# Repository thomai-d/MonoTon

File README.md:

# MonoTon
Arduino based step sequencer and software-synth

Video on youtube:

[(Audio only)](https://github.com/thomai-d/MonoTon/blob/master/media/MonoTon1.mp3).

## Features
* 8 instruments (Kick, Hat, Snare, Shaker, Clap, Noise, Sine, Square)
* Each instrument has 4 banks a 16 steps each and can be muted
* Synthesis using 8bit wavetables
* 20000Hz sampling rate
* Master is filtered through analog high-pass filter (2pole)

## Hardware
* atmega1284 @ 16MHz using [Mighty1284 platform](https://github.com/maniacbug/mighty-1284p)
* lots of 74HC595 shift registers (for LEDs)
* MCP23S17 port extenders (for buttons)
* CD4067 multiplexer (for analog potis)
* R2R network for D/A conversion
* Some eagle files included

## Lessons learned while developing
* The analog inputs are quite noisy. De-noising uses quite much cpu.
* Don't ever solder this much wires by hand. PCB services are your friend.
* Prefer [DDS](http://interface.khm.de/index.php/lab/interfaces-advanced/arduino-dds-sinewave-generator/) over an R2R ladder.

## Open bugs / flaws
* Although the output is buffered by an opamp, the sound sounds distorted when using the PC's line in. If I conntect it directly to the speakers, the sound is quite clear.

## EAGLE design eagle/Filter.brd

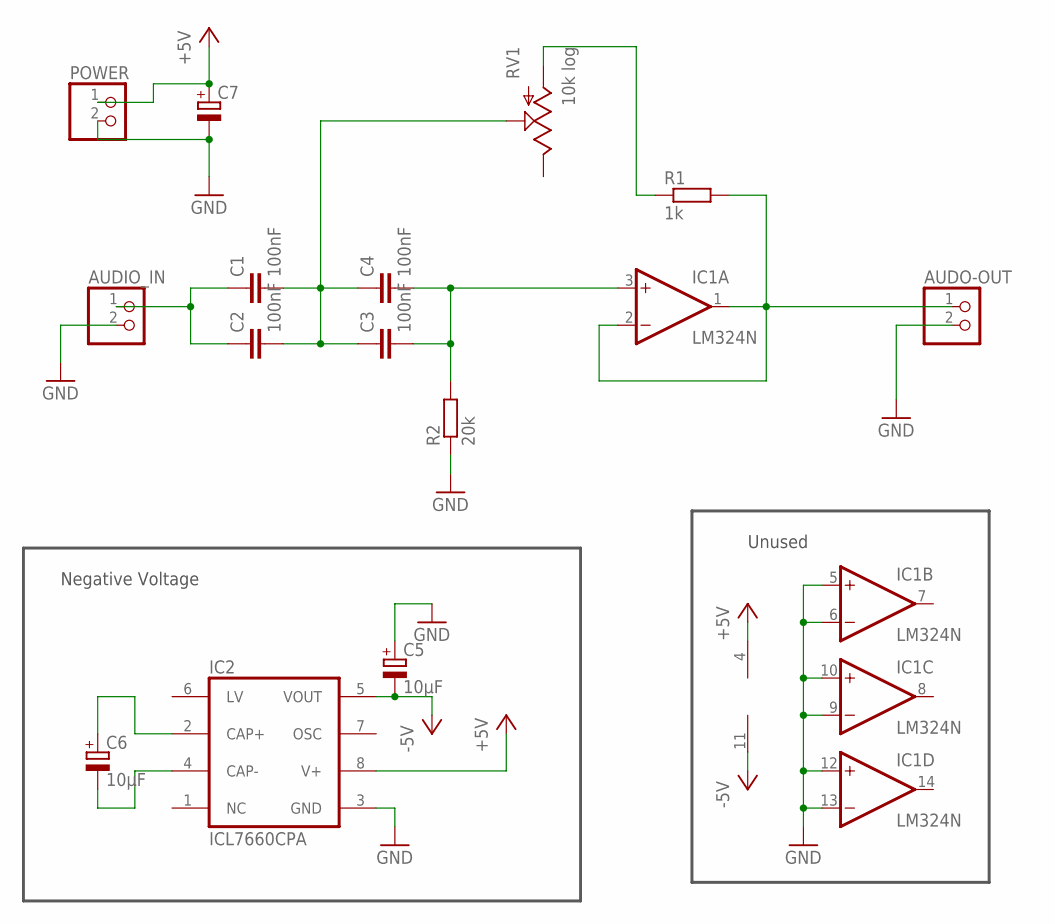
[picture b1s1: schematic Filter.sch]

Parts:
AUDIO_IN: PINHD-1X2; 1X02
AUDO-OUT: PINHD-1X2; 1X02
C1, C2, C3, C4: 100nF; C025-025X050
C5, C6: 10µF; E2,5-6
C7: CPOL-EUE2.5-6; E2,5-6
IC1: LM324N; DIL14
IC2: ICL7660CPA; DIL08
POWER: PINHD-1X2; 1X02
R1: 1k; 0207/7
R2: 20k; 0207/7
RV1: 10k log; ALPS_POT

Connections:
+5V: C7.+, IC1.4 (V+), IC2.8 (V+), POWER.1
-5V: C5.-, IC1.11 (V-), IC2.5 (VOUT)
GND: AUDIO_IN.2, AUDO-OUT.2, C5.+, C7.-, IC1.5 (+IN), IC1.6 (-IN), IC1.9 (-IN), IC1.10 (+IN), IC1.12 (+IN), IC1.13 (-IN), IC2.3 (GND), POWER.2, R2.1
unnamed: C3.2, C4.2, IC1.3 (+IN), R2.2
unnamed: AUDIO_IN.1, C1.1, C2.1
unnamed: C1.2, C2.2, C3.1, C4.1, RV1.P$2 (S)
unnamed: AUDO-OUT.1, IC1.1 (OUT), IC1.2 (-IN), R1.2
unnamed: R1.1, RV1.P$3 (A)
unnamed: C6.+, IC2.2 (CAP+)
unnamed: C6.-, IC2.4 (CAP-)

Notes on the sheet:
Unused
Negative Voltage

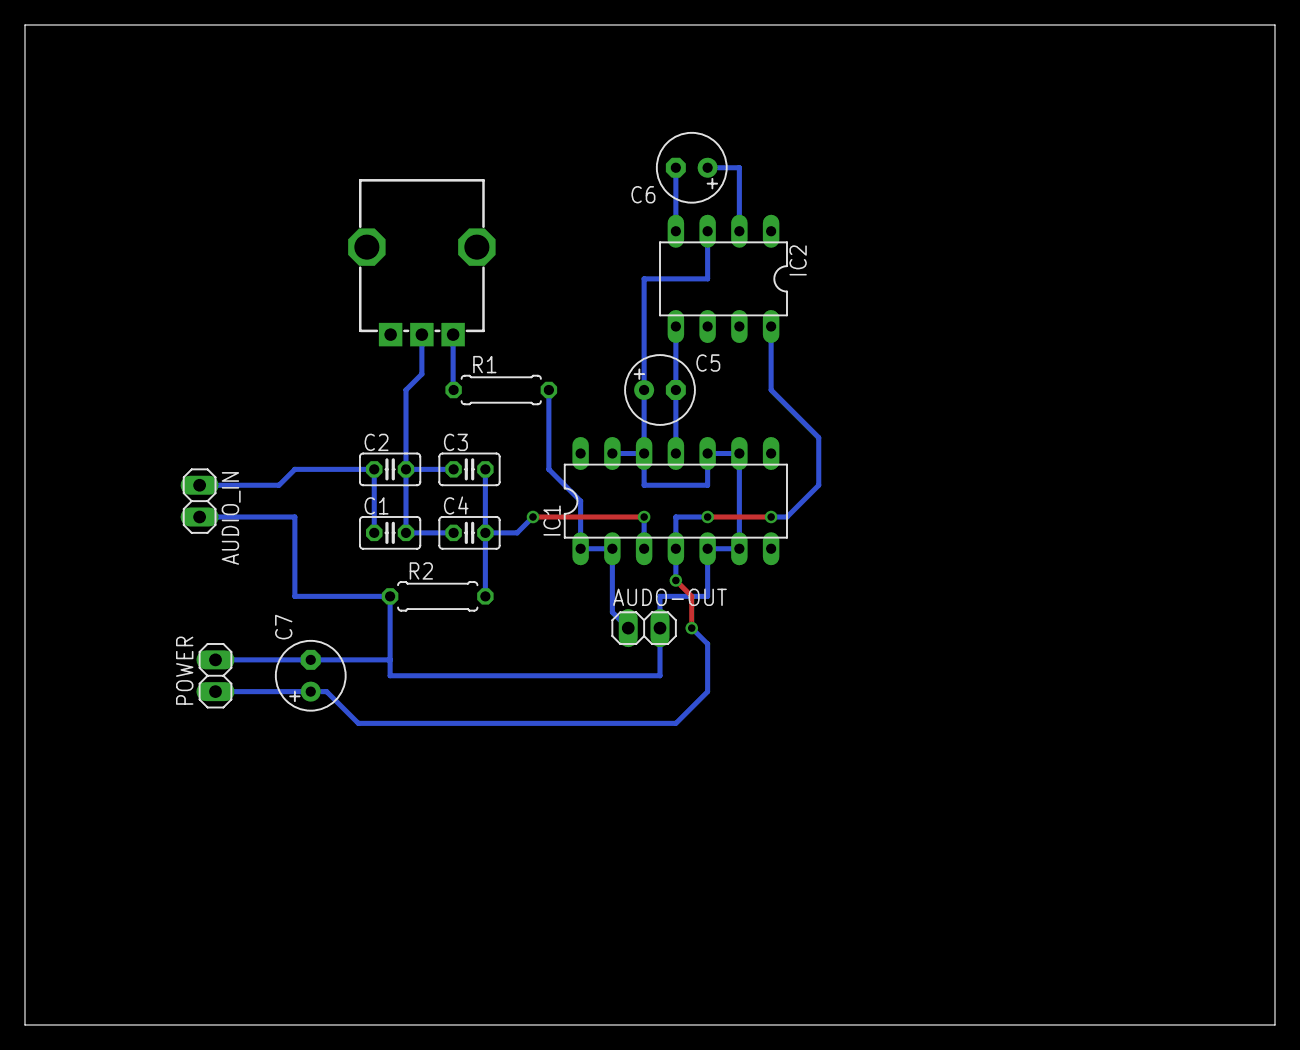
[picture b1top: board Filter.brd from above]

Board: 2 copper layers, 100.0 x 80.0 mm, 15 parts (0 on the bottom side), 10 nets.

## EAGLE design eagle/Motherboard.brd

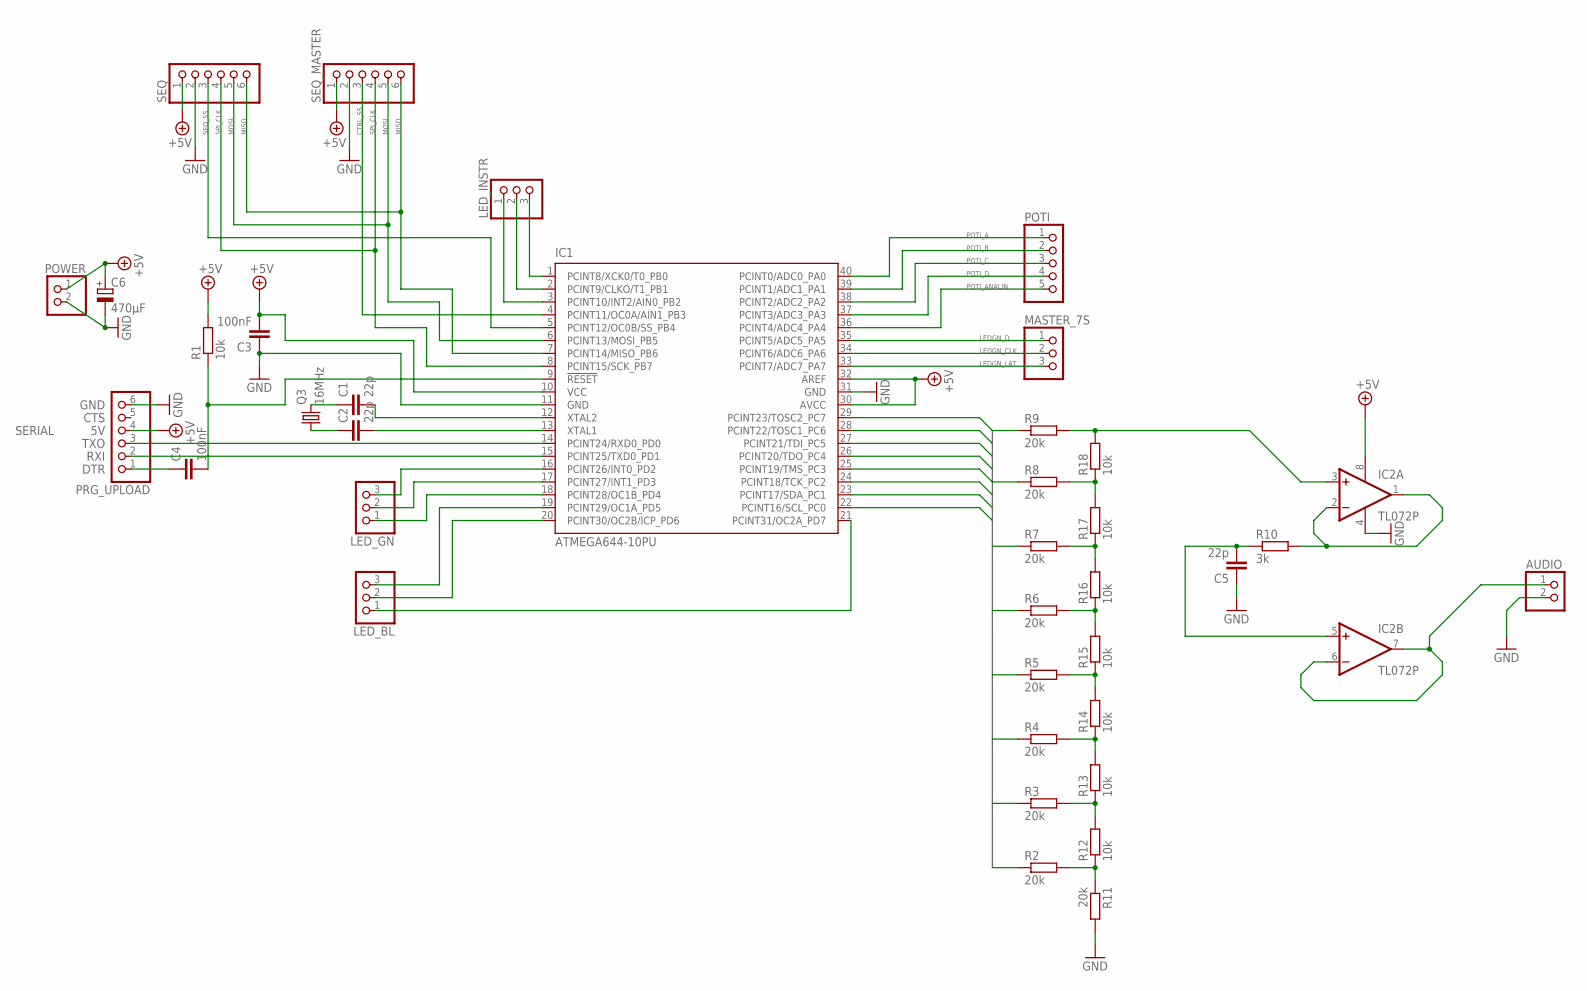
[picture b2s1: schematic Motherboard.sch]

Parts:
AUDIO: PINHD-1X2; 1X02
C1, C2, C5: 22p; C025-060X050
C3, C4: 100nF; C025-060X050
C6: 470µF; E3,5-10
IC1: ATMEGA644-10PU; DIL40
IC2: TL072P; DIL08
LED_BL: PINHD-1X3; 1X03
LED_GN: PINHD-1X3; 1X03
LED_INSTR: PINHD-1X3; 1X03
MASTER_7S: PINHD-1X3; 1X03
POTI: PINHD-1X5; 1X05
POWER: PINHD-1X2; 1X02
PRG_UPLOAD: PINHD-1X6; 1X06
Q3: 16MHz; HC18U-V
R1, R12, R13, R14, R15, R16, R17, R18: 10k; 0204/7
R2, R3, R4, R5, R6, R7, R8, R9, R11: 20k; 0204/7
R10: 3k; 0204/7
SEQ: PINHD-1X6; 1X06
SEQ_MASTER: PINHD-1X6; 1X06

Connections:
+5V: C3.2, C6.+, IC1.10 (VCC), IC1.30 (AVCC), IC1.32 (AREF), IC2.8 (V+), POWER.1, PRG_UPLOAD.4, R1.2, SEQ.1, SEQ_MASTER.1
CTRL_SS: IC1.4 (PCINT11/OC0A/AIN1_PB3), SEQ_MASTER.3
DA0: IC1.22 (PCINT16/SCL_PC0), R2.1
DA1: IC1.23 (PCINT17/SDA_PC1), R3.1
DA2: IC1.24 (PCINT18/TCK_PC2), R4.1
DA3: IC1.25 (PCINT19/TMS_PC3), R5.1
DA4: IC1.26 (PCINT20/TDO_PC4), R6.1
DA5: IC1.27 (PCINT21/TDI_PC5), R7.1
DA6: IC1.28 (PCINT22/TOSC1_PC6), R8.1
DA7: IC1.29 (PCINT23/TOSC2_PC7), R9.1
GND: AUDIO.2, C3.1, C5.1, C6.-, IC1.11 (GND), IC1.31 (GND), IC2.4 (V-), POWER.2, PRG_UPLOAD.6, R11.2, SEQ.2, SEQ_MASTER.2
LEDGN_CLK: IC1.34 (PCINT6/ADC6_PA6), MASTER_7S.2
LEDGN_D: IC1.35 (PCINT5/ADC5_PA5), MASTER_7S.1
LEDGN_LAT: IC1.33 (PCINT7/ADC7_PA7), MASTER_7S.3
MISO: IC1.7 (PCINT14/MISO_PB6), SEQ.6, SEQ_MASTER.6
MOSI: IC1.6 (PCINT13/MOSI_PB5), SEQ.5, SEQ_MASTER.5
unnamed: C1.1, Q3.2
unnamed: C2.1, Q3.1
unnamed: C2.2, IC1.13 (XTAL1)
unnamed: C1.2, IC1.12 (XTAL2)
unnamed: R3.2, R12.2, R13.1
unnamed: R4.2, R13.2, R14.1
unnamed: R5.2, R14.2, R15.1
unnamed: R6.2, R15.2, R16.1
unnamed: IC1.1 (PCINT8/XCK0/T0_PB0), LED_INSTR.3
unnamed: IC1.2 (PCINT9/CLKO/T1_PB1), LED_INSTR.2
unnamed: IC1.3 (PCINT10/INT2/AIN0_PB2), LED_INSTR.1
unnamed: R7.2, R16.2, R17.1
unnamed: R8.2, R17.2, R18.1
unnamed: R2.2, R11.1, R12.1
unnamed: IC2.3 (+IN), R9.2, R18.2
unnamed: IC2.1 (OUT), IC2.2 (-IN), R10.2
unnamed: IC1.16 (PCINT26/INT0_PD2), LED_GN.3
unnamed: IC1.17 (PCINT27/INT1_PD3), LED_GN.2
unnamed: IC1.18 (PCINT28/OC1B_PD4), LED_GN.1
unnamed: IC1.19 (PCINT29/OC1A_PD5), LED_BL.3
unnamed: IC1.20 (PCINT30/OC2B/ICP_PD6), LED_BL.2
unnamed: IC1.21 (PCINT31/OC2A_PD7), LED_BL.1
unnamed: C5.2, IC2.5 (+IN), R10.1
unnamed: AUDIO.1, IC2.6 (-IN), IC2.7 (OUT)
POTI_A: IC1.40 (PCINT0/ADC0_PA0), POTI.1
POTI_ANALIN: IC1.36 (PCINT4/ADC4_PA4), POTI.5
POTI_B: IC1.39 (PCINT1/ADC1_PA1), POTI.2
POTI_C: IC1.38 (PCINT2/ADC2_PA2), POTI.3
POTI_D: IC1.37 (PCINT3/ADC3_PA3), POTI.4
RESET: C4.2, IC1.9 (!RESET), R1.1
SEQ_SS: IC1.5 (PCINT12/OC0B/SS_PB4), SEQ.3
SPI_CLK: IC1.8 (PCINT15/SCK_PB7), SEQ.4, SEQ_MASTER.4
UPLOAD_DTR: C4.1, PRG_UPLOAD.1
UPLOAD_RXI: IC1.15 (PCINT25/TXD0_PD1), PRG_UPLOAD.2
UPLOAD_TXO: IC1.14 (PCINT24/RXD0_PD0), PRG_UPLOAD.3

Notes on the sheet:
GND
CTS
TXO
RXI
DTR
SERIAL

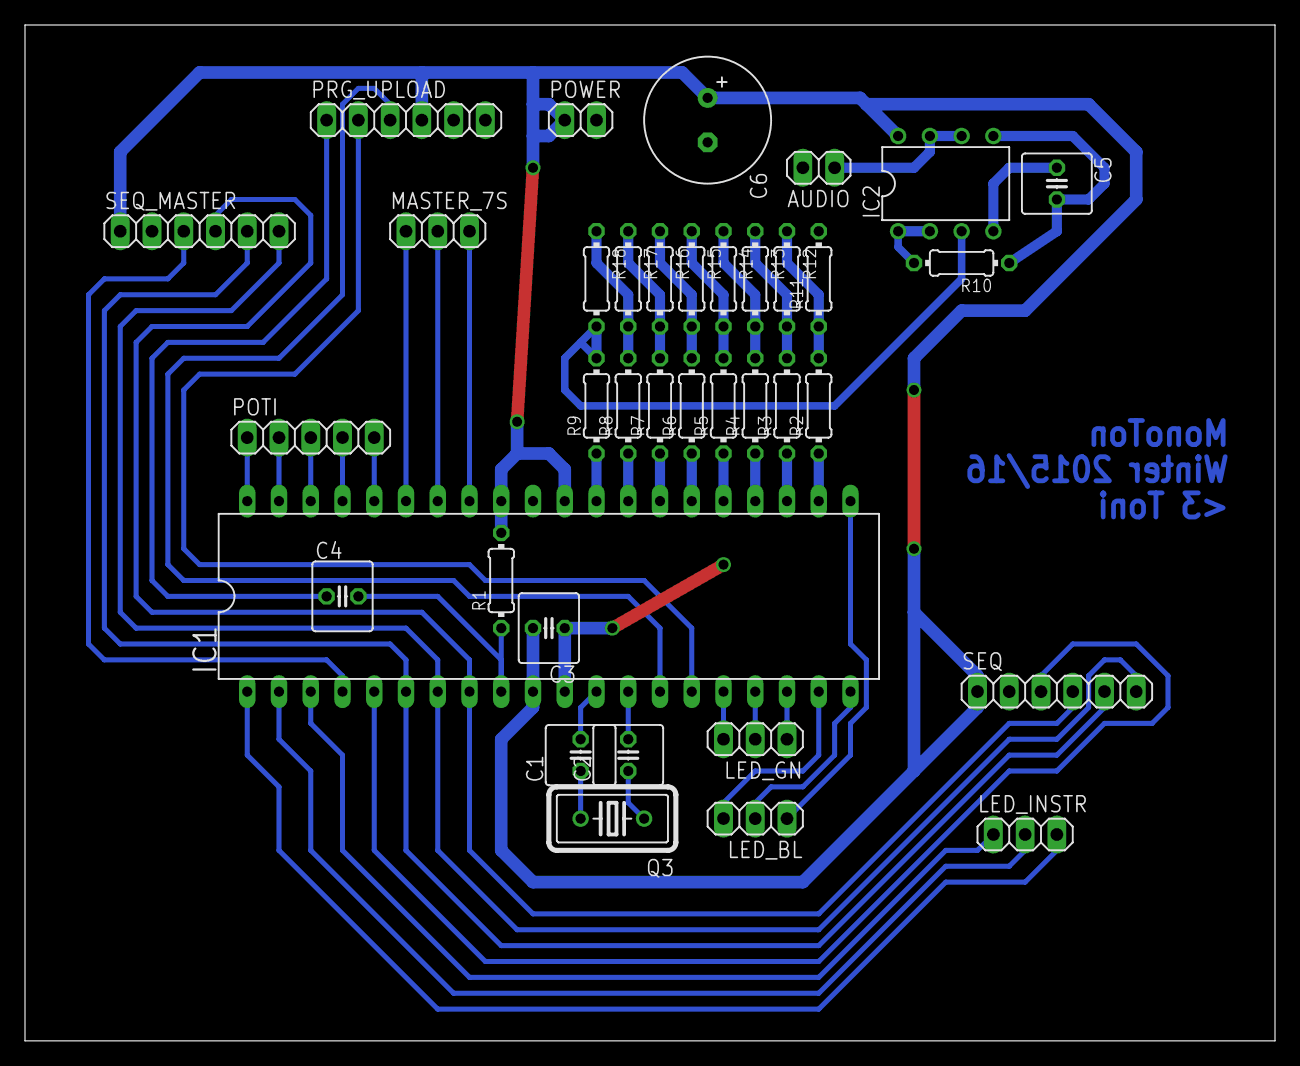
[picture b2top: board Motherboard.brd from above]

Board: 2 copper layers, 100.0 x 81.3 mm, 37 parts (0 on the bottom side), 51 nets.

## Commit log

2017-01-07 Added readme
2017-01-07 Fixed readme, added mp3
2017-01-07 Added source & eagle files
2017-01-07 Reduced image size
2017-01-07 Added video
2017-02-28 Added core image
2017-02-28 Fixed readme & image
2017-02-28 Fixed readme

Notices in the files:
parts and their libraries:
SparkFun-Electromechanical: Licensing: Creative Commons ShareAlike 4.0 International - https://creativecommons.org/licenses/by-sa/4.0
